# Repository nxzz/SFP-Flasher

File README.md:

# sfp-eerom-web

ブラウザ（WebHID）から RP2040(Pico) I2C ゲートウェイ経由で SFP モジュールの EEPROM を読み書きするツール一式。
ダンプ／解析、クローン書込（実シリアル番号を維持）、DWDM 波長設定をブラウザだけで行えます。

```
┌────────────┐   WebHID    ┌──────────────┐    I2C     ┌──────────────┐
│  ブラウザ   │ ─ 64B HID ─ │ RP2040(Pico) │ ─ 0x50/   │  SFP module  │
│ (web/)     │   レポート   │  gateway     │   0x51 ── │  EEPROM      │
└────────────┘             └──────────────┘            └──────────────┘
```

## 構成

| ディレクトリ | 内容 |
|---|---|
| [`web/`](web/) | WebHID Web アプリ（Firebase Hosting にデプロイ）。ダンプ／クローン書込／DWDM 設定。詳細は [`web/README.md`](web/README.md) |
| [`device-src/`](device-src/) | RP2040(Pico) ゲートウェイのファームウェア（PlatformIO / arduino-pico コア） |

## WebHID ⇄ I2C プロトコル

64 バイト固定の HID IN/OUT レポートでコマンドをやり取りする汎用 I2C ゲートウェイです。
2 系統の I2C バスに対応します（bus0 = SDA/SCL = IO12/IO13、bus1 = IO26/IO27）。

OUT レポート（ブラウザ → デバイス, 64B）:

| オフセット | 内容 |
|---|---|
| `[0]` seq | 任意のシーケンス番号（応答にそのままエコー） |
| `[1]` cmd | `0x00` PING / `0x01` READ / `0x02` WRITE / `0x03` SCAN |
| `[2]` bus | 0 or 1 |
| `[3]` addr | 7bit I2C アドレス |
| `[4]` reg | レジスタ／オフセット（READ/WRITE 開始位置） |
| `[5]` len | READ=読み出しバイト数 / WRITE=書き込みバイト数 |
| `[6..]` | WRITE データ |

IN レポート（デバイス → ブラウザ, 64B）:

| オフセット | 内容 |
|---|---|
| `[0]` seq | 要求の seq をエコー |
| `[1]` status | `0x00` OK / `0x01` NACK / `0x02` BADARG / `0x03` TOOBIG |
| `[2]` len | 有効データ長 |
| `[3..]` | データ（READ=読み出し値 / SCAN=見つかったアドレス列 / PING=版数） |

- READ は 1 回最大 61 バイト、WRITE は 1 回最大 58 バイト。
- WRITE は 8 バイトページ境界を跨がないよう Web アプリ側で自動分割します（24Cxx 系 EEPROM 対策）。

## デバイスのビルド／書き込み

[PlatformIO](https://platformio.org/) を使用します（arduino-pico / Earle Philhower コア、USB スタックは Adafruit TinyUSB）。

```bash
cd device-src
pio run                 # ビルド
pio run --target upload  # Pico へ書き込み（BOOTSEL でマウント）
```

## Web アプリの実行

```bash
cd web
npx serve .
#  → 表示された http://localhost:xxxx を Chrome / Edge で開く
```

デプロイ手順や機能の詳細は [`web/README.md`](web/README.md) を参照してください。

## 動作要件

- **Chrome / Edge など Chromium 系ブラウザ**（WebHID 対応。iOS Safari は非対応。Android Chrome は対応）
- RP2040(Pico) ゲートウェイ（`device-src/` のファームウェアを書き込んだもの）

## 注意

クローン書込は SFP の EEPROM を上書きします。先に「ダンプ／解析」でバックアップを取得してください。

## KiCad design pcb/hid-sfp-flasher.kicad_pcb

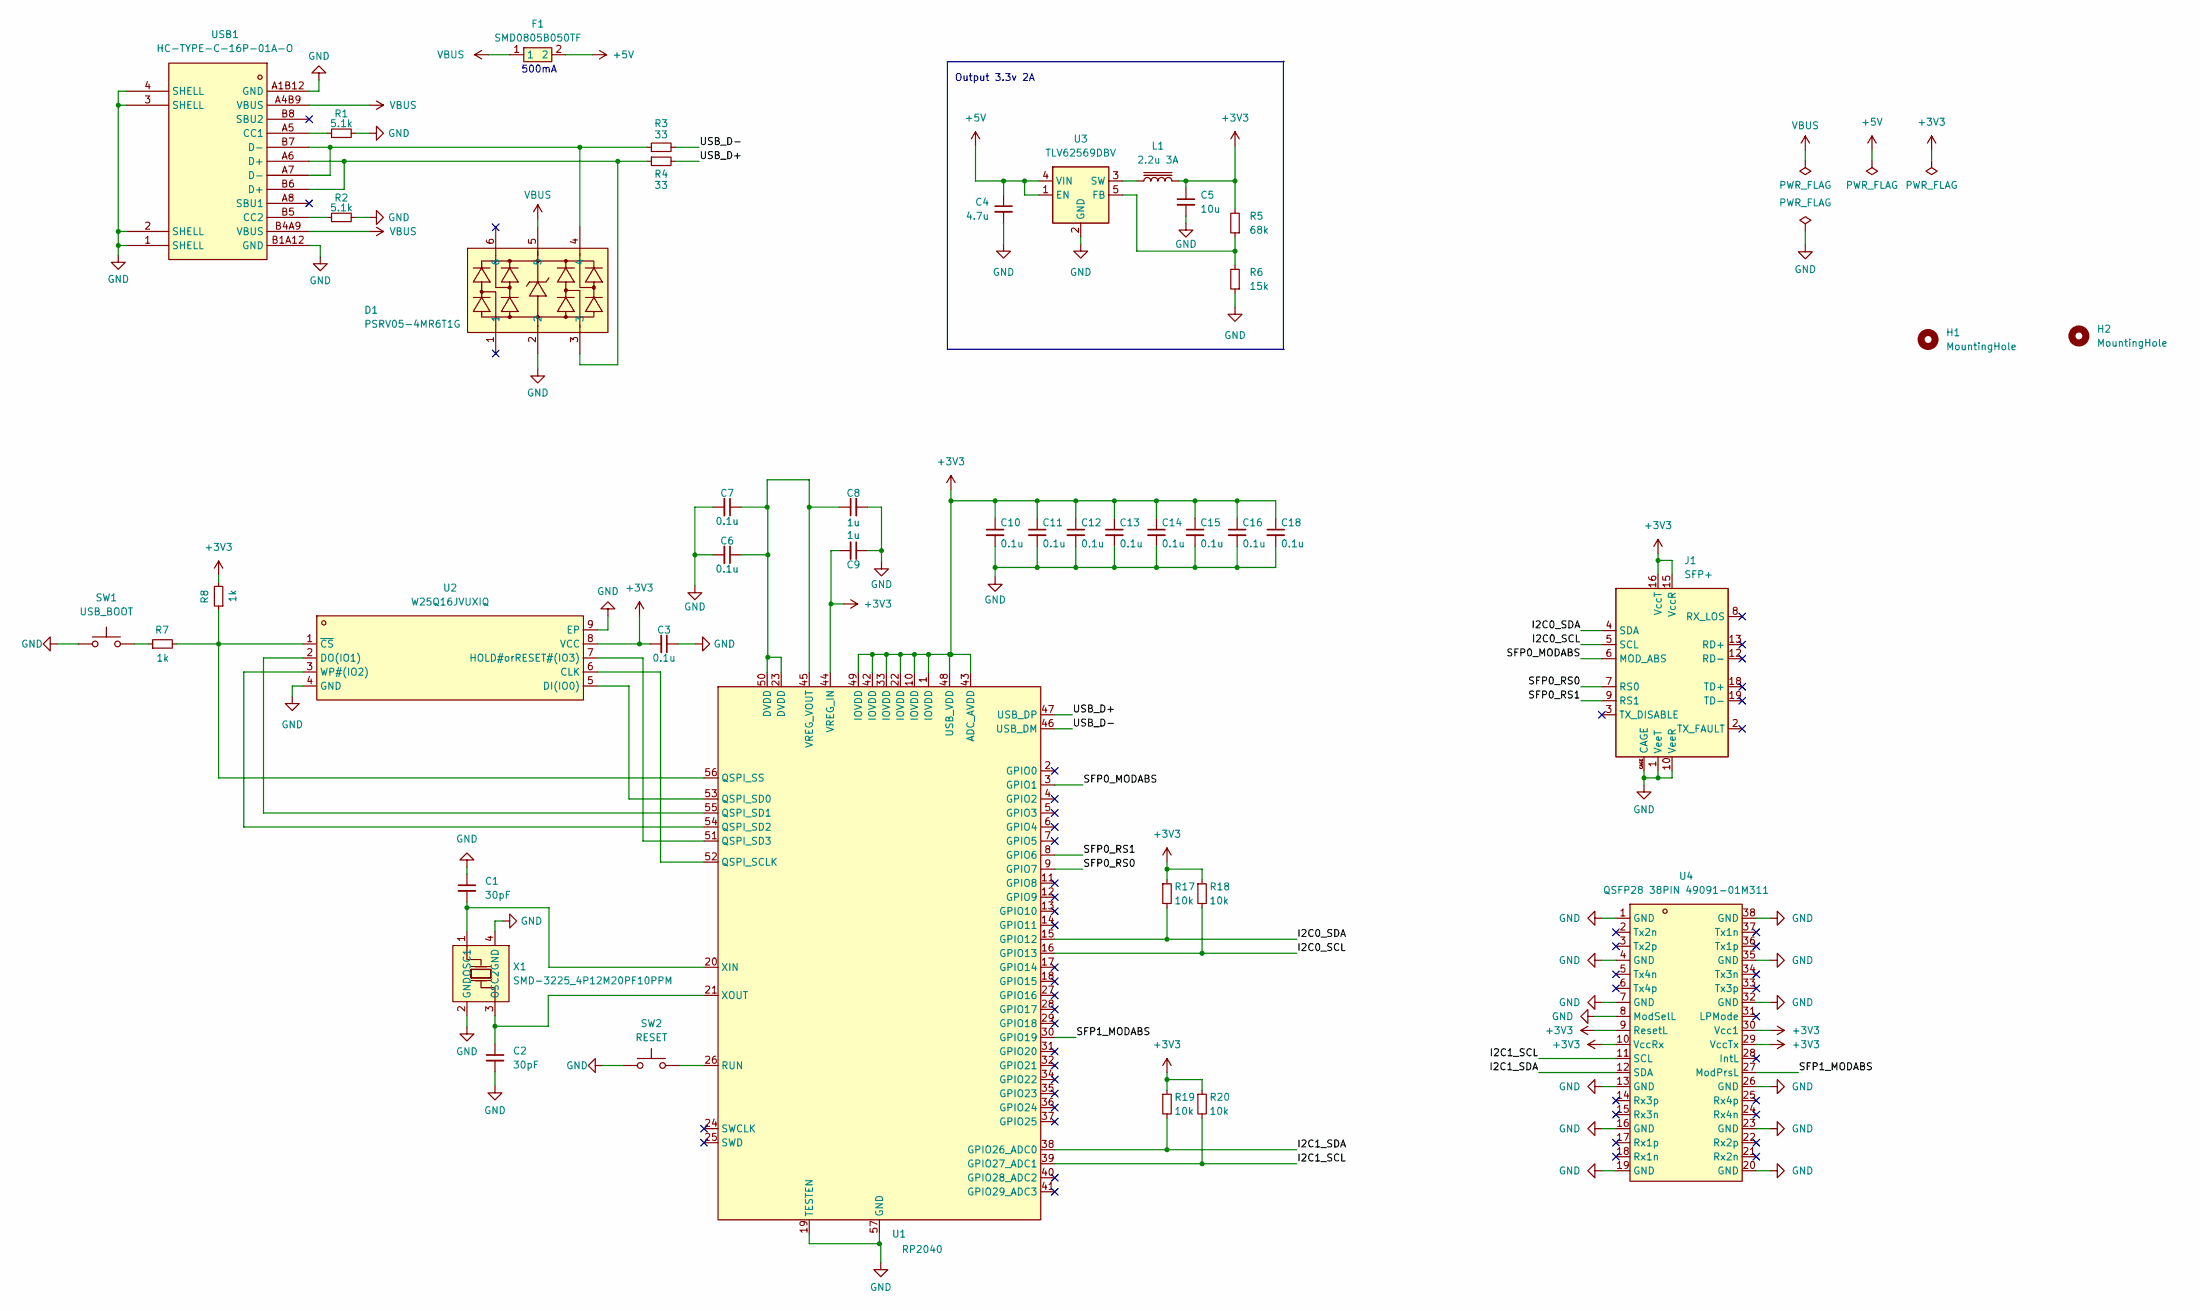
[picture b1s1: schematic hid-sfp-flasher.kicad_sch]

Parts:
C1, C2: 30pF; C_0603_1608Metric; LCSC Part C1658
C3, C6, C7, C10, C11, C12, C13, C14, C15, C16, C18: 0.1u; C_0402_1005Metric; LCSC Part C1525
C4: 4.7u; C_0603_1608Metric; LCSC C19666
C5: 10u; C_0603_1608Metric; LCSC C19702
C8, C9: 1u; C_0402_1005Metric; LCSC C52923
D1: PSRV05-4MR6T1G; SOT-23-6_L2.9-W1.6-P0.95-LS2.8-BL; LCSC Part C2936987
F1: SMD0805B050TF; F0805; LCSC Part C269104
H1, H2: MountingHole; MountingHole_3.2mm_M3
J1: SFP+; SFP20P
L1: 2.2u 3A; CMLW4030S2R2MST; LCSC C431273
R1, R2: 5.1k; R_0402_1005Metric; LCSC Part C25905
R3, R4: 33; R_0402_1005Metric; LCSC Part C25105
R5: 68k; R_0603_1608Metric; LCSC C23231
R6: 15k; R_0603_1608Metric; LCSC C22809
R7, R8: 1k; R_0402_1005Metric; LCSC C11702
R17, R18, R19, R20: 10k; R_0402_1005Metric; LCSC C25744
SW1: USB_BOOT; SW_SPST_PTS810; LCSC C470427
SW2: RESET; SW_SPST_PTS810; LCSC C470427
U1: RP2040; LQFN-56_L7.0-W7.0-P0.4-EP; LCSC Part C2040
U2: W25Q16JVUXIQ; USON-8_L3.0-W2.0-P0.50-BL-EP; LCSC Part C2843335
U3: TLV62569DBV; SOT-23-5; LCSC C141836
U4: QSFP28 38PIN 49091-01M311; CONN-SMD_38P-P0.80_TE_1551920-2; MPN QSFP28 38PIN 49091-01M311; LCSC Part C50159077
USB1: HC-TYPE-C-16P-01A-O; USB-C-SMD_G-SWITCH_GT-USB-7010EN; LCSC Part C2997434
X1: SMD-3225_4P12M20PF10PPM; CRYSTAL-SMD_4P-L3.2-W2.5-BL; LCSC Part C133334

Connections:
+3V3: C3.2, C5.1, C9.2, C10.1, C11.1, C12.1, C13.1, C14.1, C15.1, C16.1, C18.1, J1.15 (VccR), J1.16 (VccT), L1.2, R5.2, R8.2, R17.1, R18.1, R19.1, R20.1, U1.1 (IOVDD), U1.10 (IOVDD), U1.22 (IOVDD), U1.33 (IOVDD), U1.42 (IOVDD), U1.43 (ADC_AVDD), U1.44 (VREG_IN), U1.48 (USB_VDD), U1.49 (IOVDD), U2.8 (VCC), U4.9 (ResetL), U4.10 (VccRx), U4.29 (VccTx), U4.30 (Vcc1)
+5V: C4.1, F1.2, U3.1 (EN), U3.4 (VIN)
/I2C0_SCL: J1.5 (SCL), R18.2, U1.16 (GPIO13)
/I2C0_SDA: J1.4 (SDA), R17.2, U1.15 (GPIO12)
/I2C1_SCL: R20.2, U1.39 (GPIO27_ADC1), U4.11 (SCL)
/I2C1_SDA: R19.2, U1.38 (GPIO26_ADC0), U4.12 (SDA)
/SFP0_MODABS: J1.6 (MOD_ABS), U1.3 (GPIO1)
/SFP0_RS0: J1.7 (RS0), U1.9 (GPIO7)
/SFP0_RS1: J1.9 (RS1), U1.8 (GPIO6)
/SFP1_MODABS: U1.30 (GPIO19), U4.27 (ModPrsL)
/USB_D+: R4.2, U1.47 (USB_DP)
/USB_D-: R3.2, U1.46 (USB_DM)
GND: C1.1, C2.2, C3.1, C4.2, C5.2, C6.2, C7.2, C8.2, C9.1, C10.2, C11.2, C12.2, C13.2, C14.2, C15.2, C16.2, C18.2, D1.2, J1.1 (VeeT), J1.10 (VeeR), J1.11 (VeeR), J1.14 (VeeR), J1.17 (VeeT), J1.20 (VeeT), J1.CAGE, R1.2, R2.2, R6.1, SW1.2, SW2.2, U1.19 (TESTEN), U1.57 (GND), U2.4 (GND), U2.9 (EP), U3.2 (GND), U4.1 (GND), U4.4 (GND), U4.7 (GND), U4.8 (ModSelL), U4.13 (GND), U4.16 (GND), U4.19 (GND), U4.20 (GND), U4.23 (GND), U4.26 (GND), U4.32 (GND), U4.35 (GND), U4.38 (GND), USB1.1 (SHELL), USB1.2 (SHELL), USB1.3 (SHELL), USB1.4 (SHELL), USB1.A1B12 (GND), USB1.B1A12 (GND), X1.2 (GND), X1.4 (GND)
unnamed: D1.3, R4.1, USB1.A6 (D+), USB1.B6 (D+)
unnamed: D1.4, R3.1, USB1.A7 (D-), USB1.B7 (D-)
unnamed: R7.1, SW1.1
unnamed: U1.52 (QSPI_SCLK), U2.6 (CLK)
unnamed: U1.53 (QSPI_SD0), U2.5 (DI(IO0))
unnamed: U1.55 (QSPI_SD1), U2.2 (DO(IO1))
unnamed: U1.54 (QSPI_SD2), U2.3 (WP#(IO2))
unnamed: U1.51 (QSPI_SD3), U2.7 (HOLD#orRESET#(IO3))
unnamed: R7.2, R8.1, U1.56 (QSPI_SS), U2.1 (~CS)
unnamed: SW2.1, U1.26 (RUN)
unnamed: C6.1, C7.1, C8.1, U1.23 (DVDD), U1.45 (VREG_VOUT), U1.50 (DVDD)
unnamed: C1.2, U1.20 (XIN), X1.1 (OSC1)
unnamed: C2.1, U1.21 (XOUT), X1.3 (OSC2)
unnamed: R5.1, R6.2, U3.5 (FB)
unnamed: L1.1, U3.3 (SW)
unnamed: R1.1, USB1.A5 (CC1)
unnamed: R2.1, USB1.B5 (CC2)
VBUS: D1.5, F1.1, USB1.A4B9 (VBUS), USB1.B4A9 (VBUS)

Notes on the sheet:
Output 3.3v 2A
500mA

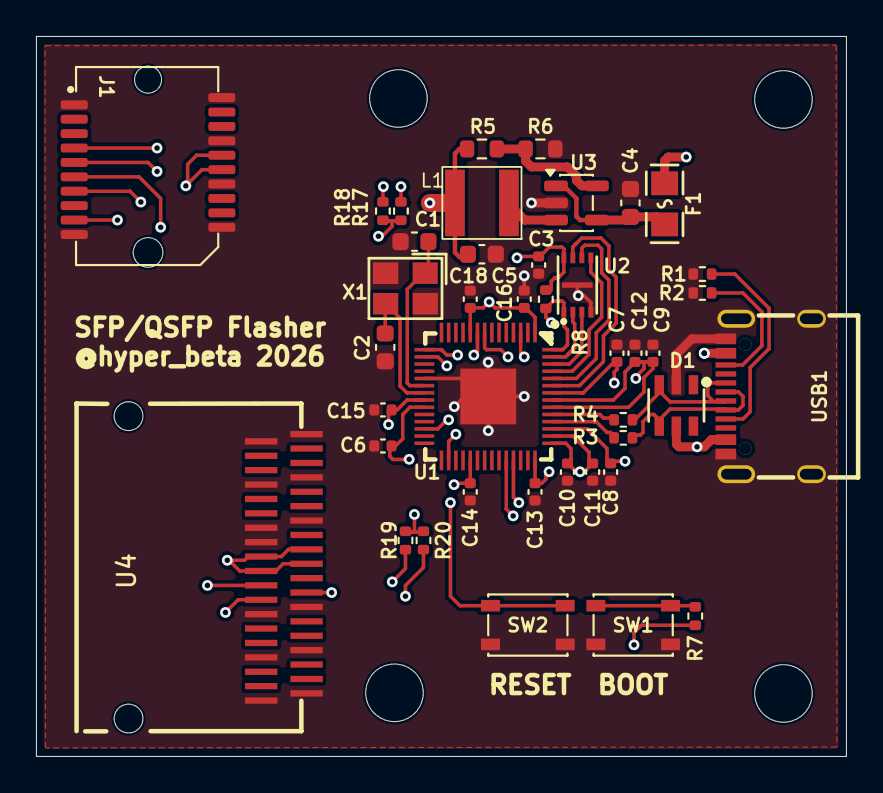
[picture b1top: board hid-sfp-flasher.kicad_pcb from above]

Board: 4 copper layers, 45.0 x 40.0 mm, 45 parts (0 on the bottom side), 31 nets.

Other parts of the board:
H1#2, H1#3: MountingHole; MountingHole_3.2mm_M3

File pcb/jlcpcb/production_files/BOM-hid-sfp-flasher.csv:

Comment,Designator,Footprint,LCSC,Quantity
0.1u,"C10,C11,C12,C13,C14,C15,C16,C18,C3,C6,C7",C_0402_1005Metric,C1525,11
10k,"R17,R18,R19,R20",R_0402_1005Metric,C25744,4
10u,C5,C_0603_1608Metric,C19702,1
15k,R6,R_0603_1608Metric,C22809,1
1k,"R7,R8",R_0402_1005Metric,C11702,2
1u,"C8,C9",C_0402_1005Metric,C52923,2
2.2u 3A,L1,CMLW4030S2R2MST,C431273,1
30pF,"C1,C2",C_0603_1608Metric,C1658,2
33,"R3,R4",R_0402_1005Metric,C25105,2
4.7u,C4,C_0603_1608Metric,C19666,1
5.1k,"R1,R2",R_0402_1005Metric,C25905,2
68k,R5,R_0603_1608Metric,C23231,1
HC-TYPE-C-16P-01A-O,USB1,USB-C-SMD_G-SWITCH_GT-USB-7010EN,C2997434,1
PSRV05-4MR6T1G,D1,SOT-23-6_L2.9-W1.6-P0.95-LS2.8-BL,C2936987,1
QSFP28 38PIN 49091-01M311,U4,CONN-SMD_38P-P0.80_TE_1551920-2,C50159077,1
RESET,SW2,SW_SPST_PTS810,C470427,1
RP2040,U1,LQFN-56_L7.0-W7.0-P0.4-EP,C2040,1
SFP+,J1,SFP20P,C42418480,1
SMD-3225_4P12M20PF10PPM,X1,CRYSTAL-SMD_4P-L3.2-W2.5-BL,C133334,1
SMD0805B050TF,F1,F0805,C269104,1
TLV62569DBV,U3,SOT-23-5,C141836,1
USB_BOOT,SW1,SW_SPST_PTS810,C470427,1
W25Q16JVUXIQ,U2,USON-8_L3.0-W2.0-P0.50-BL-EP,C2843335,1

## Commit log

2026-06-04 device init
2026-06-04 web init
2026-06-04 readme
2026-06-05 AvagoとかFinのパスワードつきとか
2026-06-13 Avago用のISP対応
2026-06-20 add kicad prj
2026-06-20 ケースのモデル
